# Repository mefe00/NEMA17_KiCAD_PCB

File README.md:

# NEMA17_KiCAD_PCB

Kartın üzerinde kullanılan bazı komponentlerin yanlış seçilmesinden dolayı kartın montajı gerçekleştirilemiyor. Aslında sadece TMC2208'in shild olarak seçilmesinden kaynaklı pin delikleri yanlış seçilmiştir. Kartın ikinci versiyonunda shild ve direkt TMC2208 çipi kullanılarak kart yenilenecektir.

V2 buradan paylaşılacaktır.

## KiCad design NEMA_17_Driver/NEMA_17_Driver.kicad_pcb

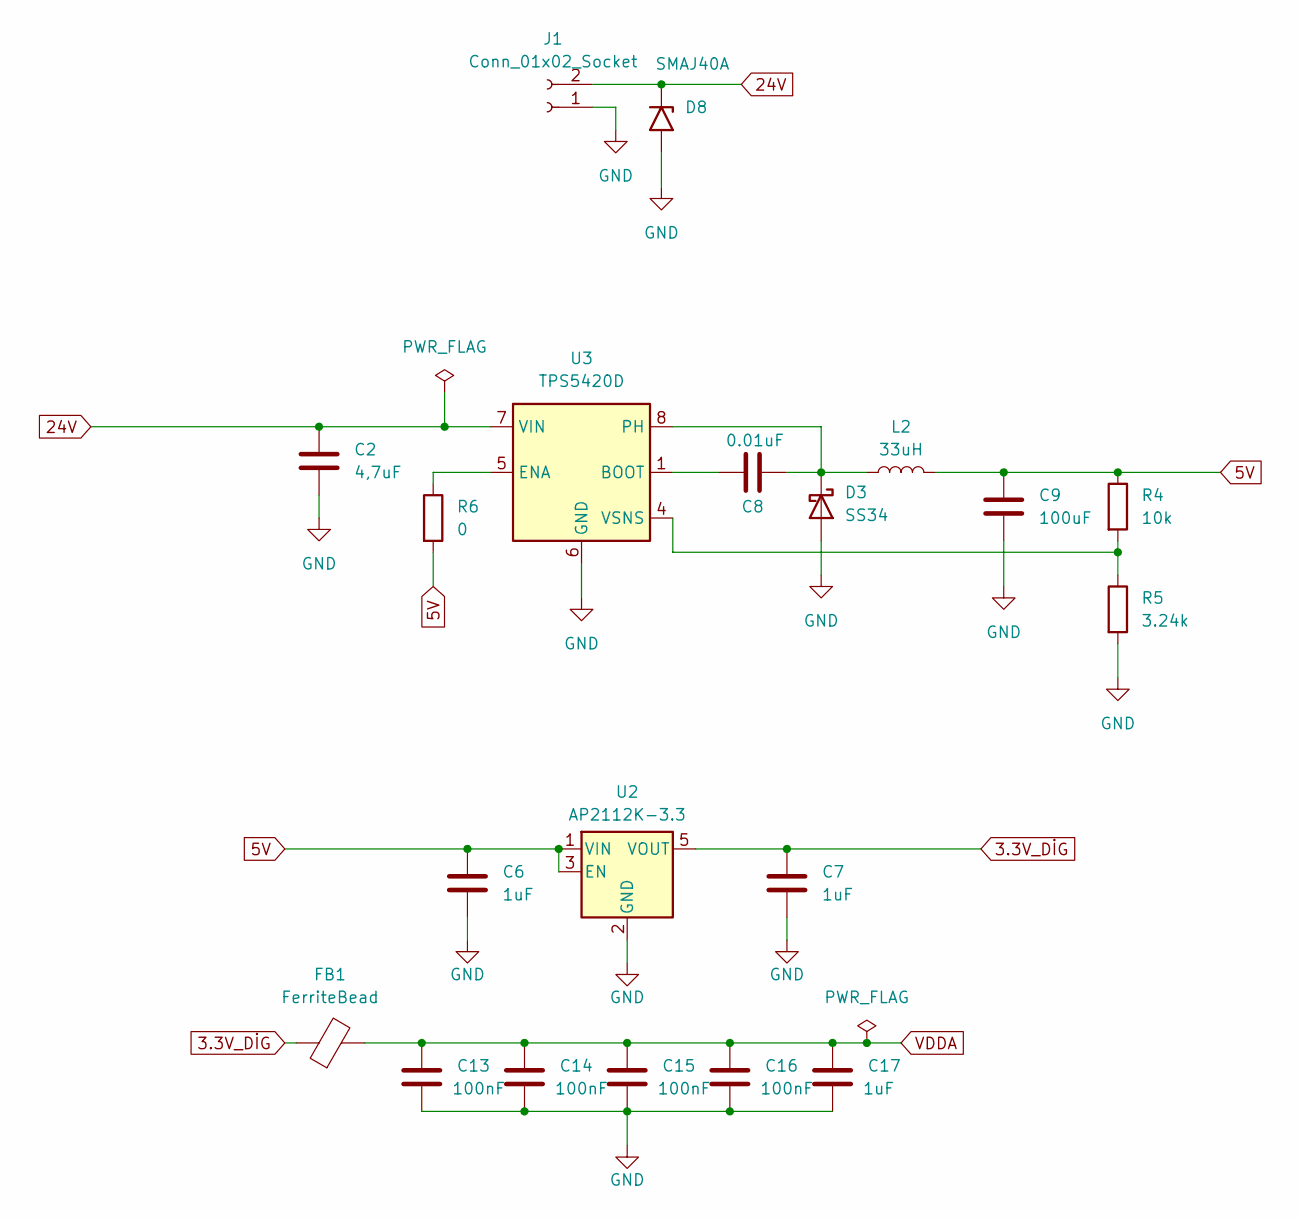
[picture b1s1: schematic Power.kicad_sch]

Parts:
C2: 4,7uF; C_Elec_8x10.2
C6, C7, C17: 1uF; C_0402_1005Metric
C8: 0.01uF; C_0603_1608Metric
C9: 100uF; C_0805_2012Metric
C13, C14, C15, C16: 100nF; C_0402_1005Metric
D3: SS34; D_SMA
D8: SMAJ40A; D_SMA
FB1: FerriteBead; L_0402_1005Metric
J1: Conn_01x02_Socket; SolderWire-0.75sqmm_1x02_P7mm_D1.25mm_OD3.5mm
L2: 33uH; L_Murata_DEM3512C
R4: 10k; R_0402_1005Metric
R5: 3.24k; R_0402_1005Metric
R6: 0; D_0201_0603Metric
U2: AP2112K-3.3; SOT-23-5
U3: TPS5420D; SOIC-8_3.9x4.9mm_P1.27mm

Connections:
3.3V_DİG: C7.1, FB1.1, U2.5 (VOUT); also elsewhere on the board
5V: C6.1, C9.1, L2.2, R4.1, R6.2, U2.1 (VIN), U2.3 (EN); also elsewhere on the board
24V: C2.1, D8.1 (A1), J1.2, U3.7 (VIN); also elsewhere on the board
GND: C2.2, C6.2, C7.2, C9.2, C13.2, C14.2, C15.2, C16.2, C17.2, D3.2 (A), D8.2 (A2), J1.1, R5.2, U2.2 (GND), U3.6 (GND); also elsewhere on the board
unnamed: C8.2, D3.1 (K), L2.1, U3.8 (PH)
unnamed: C8.1, U3.1 (BOOT)
unnamed: R6.1, U3.5 (ENA)
unnamed: R4.2, R5.1, U3.4 (VSNS)
VDDA: C13.1, C14.1, C15.1, C16.1, C17.1, FB1.2; also elsewhere on the board

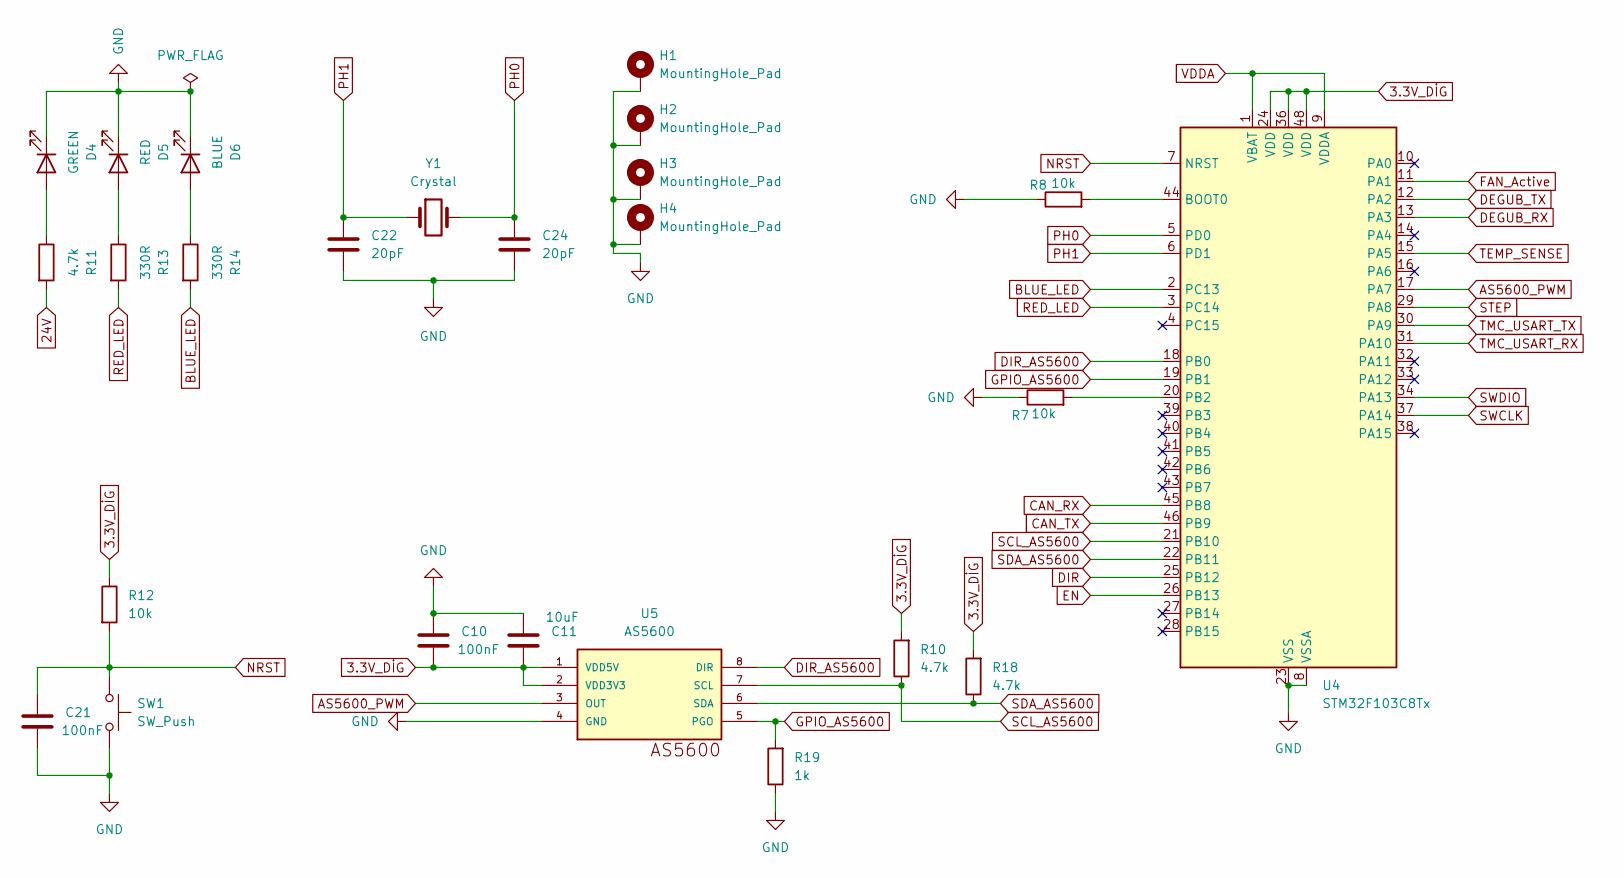
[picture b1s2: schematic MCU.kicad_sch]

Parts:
C10, C21: 100nF; C_0402_1005Metric
C11: 10uF; C_0402_1005Metric
C22, C24: 20pF; C_0603_1608Metric
D4: GREEN; LED_0402_1005Metric
D5: RED; LED_0402_1005Metric
D6: BLUE; LED_0402_1005Metric
H1, H2, H3, H4: MountingHole_Pad; MountingHole_3.5mm_Pad_Via
R7, R8, R12: 10k; R_0402_1005Metric
R10, R18: 4.7k; R_0402_1005Metric
R11: 4.7k; R_0603_1608Metric
R13, R14: 330R; R_0402_1005Metric
R19: 1k; R_0402_1005Metric
SW1: SW_Push; SW_Push_1P1T_NO_CK_KMR2
U4: STM32F103C8Tx; LQFP-48_7x7mm_P0.5mm
U5: AS5600; SOIC8
Y1: Crystal; Crystal_SMD_5032-2Pin_5.0x3.2mm

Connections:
3.3V_DİG: C10.2, C11.2, R10.2, R12.1, R18.2, U4.24 (VDD), U4.36 (VDD), U4.48 (VDD), U5.1 (VDD5V), U5.2 (VDD3V3); also elsewhere on the board
24V: R11.2; also elsewhere on the board
AS5600_PWM: U4.17 (PA7), U5.3 (OUT)
BLUE_LED: R14.2, U4.2 (PC13)
CAN_RX: U4.45 (PB8); also elsewhere on the board
CAN_TX: U4.46 (PB9); also elsewhere on the board
DEGUB_RX: U4.13 (PA3); also elsewhere on the board
DEGUB_TX: U4.12 (PA2); also elsewhere on the board
DIR: U4.25 (PB12); also elsewhere on the board
DIR_AS5600: U4.18 (PB0), U5.8 (DIR)
EN: U4.26 (PB13); also elsewhere on the board
FAN_Active: U4.11 (PA1); also elsewhere on the board
GND: C10.1, C11.1, C21.2, C22.2, C24.2, D4.1 (K), D5.1 (K), D6.1 (K), H1.1, H2.1, H3.1, H4.1, R7.1, R8.1, R19.1, SW1.2, U4.8 (VSSA), U4.23 (VSS), U4.35 (VSS), U4.47 (VSS), U5.4 (GND); also elsewhere on the board
GPIO_AS5600: R19.2, U4.19 (PB1), U5.5 (PGO)
NRST: C21.1, R12.2, SW1.1, U4.7 (NRST)
unnamed: D4.2 (A), R11.1
unnamed: D5.2 (A), R13.1
unnamed: D6.2 (A), R14.1
unnamed: R8.2, U4.44 (BOOT0)
unnamed: R7.2, U4.20 (PB2)
PH0: C24.1, U4.5 (PD0), Y1.2
PH1: C22.1, U4.6 (PD1), Y1.1
RED_LED: R13.2, U4.3 (PC14)
SCL_AS5600: R10.1, U4.21 (PB10), U5.7 (SCL)
SDA_AS5600: R18.1, U4.22 (PB11), U5.6 (SDA)
STEP: U4.29 (PA8); also elsewhere on the board
SWCLK: U4.37 (PA14); also elsewhere on the board
SWDIO: U4.34 (PA13); also elsewhere on the board
TEMP_SENSE: U4.15 (PA5); also elsewhere on the board
TMC_USART_RX: U4.31 (PA10); also elsewhere on the board
TMC_USART_TX: U4.30 (PA9); also elsewhere on the board
VDDA: U4.1 (VBAT), U4.9 (VDDA); also elsewhere on the board

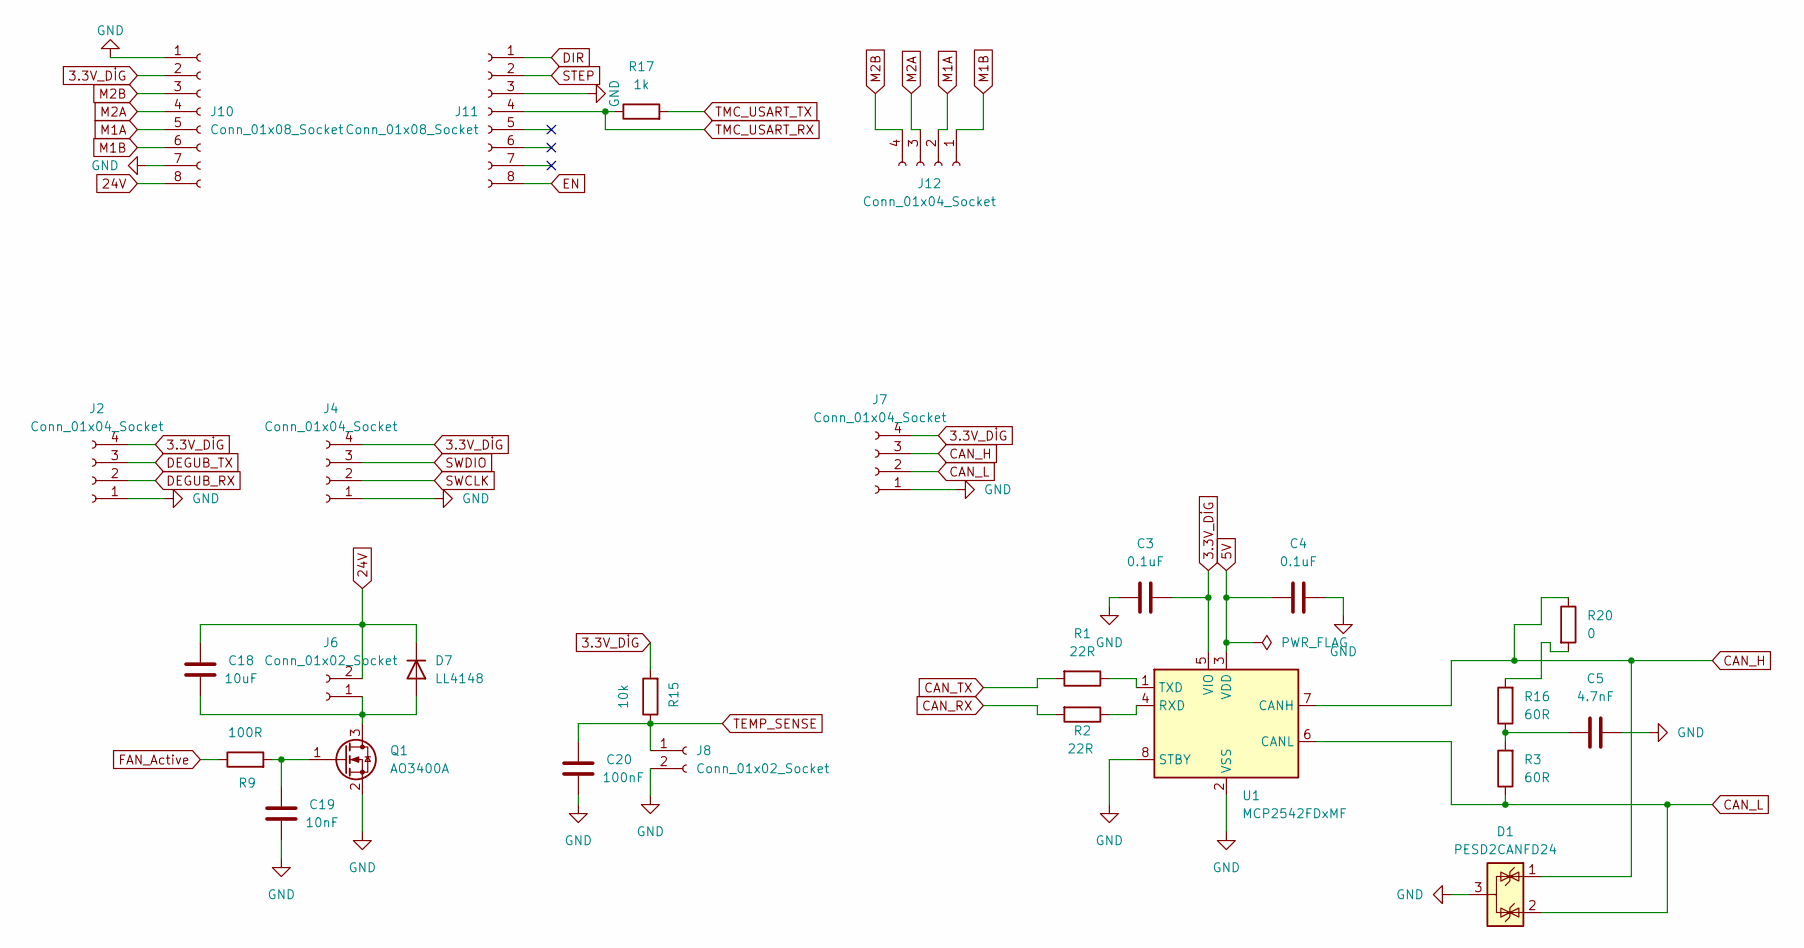
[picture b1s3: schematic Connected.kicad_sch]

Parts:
C3, C4: 0.1uF; C_0402_1005Metric
C5: 4.7nF; C_0402_1005Metric
C18: 10uF; C_0402_1005Metric
C19: 10nF; C_0402_1005Metric
C20: 100nF; C_0402_1005Metric
D1: PESD2CANFD24
D7: LL4148; D_MiniMELF
J2, J4: Conn_01x04_Socket; Hirose_DF13-04P-1.25DSA_1x04_P1.25mm_Vertical
J6, J8: Conn_01x02_Socket; Hirose_DF13-02P-1.25DSA_1x02_P1.25mm_Vertical
J7: Conn_01x04_Socket; Hirose_DF13-04P-1.25DS_1x04_P1.25mm_Horizontal
J10, J11: Conn_01x08_Socket; PinSocket_1x08_P2.00mm_Vertical
J12: Conn_01x04_Socket; Molex_KK-254_AE-6410-04A_1x04_P2.54mm_Vertical
Q1: AO3400A; SOT-23
R1, R2: 22R; R_0402_1005Metric
R3, R16: 60R; R_0402_1005Metric
R9: 100R; R_0402_1005Metric
R15: 10k; R_0402_1005Metric
R17: 1k; R_0402_1005Metric
R20: 0; R_0201_0603Metric
U1: MCP2542FDxMF; DFN-8-1EP_3x3mm_P0.65mm_EP1.55x2.4mm

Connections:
3.3V_DİG: C3.2, J2.4, J4.4, J7.4, J10.2, R15.2, U1.5 (VIO); also elsewhere on the board
5V: C4.1, U1.3 (VDD); also elsewhere on the board
24V: C18.1, D7.1 (K), J6.2, J10.8; also elsewhere on the board
CAN_H: D1.1 (K), J7.3, R20.1, U1.7 (CANH)
CAN_L: D1.2 (K), J7.2, R3.1, U1.6 (CANL)
CAN_RX: R2.2; also elsewhere on the board
CAN_TX: R1.2; also elsewhere on the board
DEGUB_RX: J2.2; also elsewhere on the board
DEGUB_TX: J2.3; also elsewhere on the board
DIR: J11.1; also elsewhere on the board
EN: J11.8; also elsewhere on the board
FAN_Active: R9.1; also elsewhere on the board
GND: C3.1, C4.2, C5.2, C19.2, C20.2, D1.3 (A), J2.1, J4.1, J7.1, J8.2, J10.1, J10.7, J11.3, Q1.2 (S), U1.2 (VSS), U1.8 (STBY), U1.9 (VSS); also elsewhere on the board
M1A: J10.5, J12.2
M1B: J10.6, J12.1
M2A: J10.4, J12.3
M2B: J10.3, J12.4
unnamed: C5.1, R3.2, R16.1
unnamed: C18.2, D7.2 (A), J6.1, Q1.3 (D)
unnamed: C19.1, Q1.1 (G), R9.2
unnamed: R16.2, R20.2
unnamed: R2.1, U1.4 (RXD)
unnamed: R1.1, U1.1 (TXD)
STEP: J11.2; also elsewhere on the board
SWCLK: J4.2; also elsewhere on the board
SWDIO: J4.3; also elsewhere on the board
TEMP_SENSE: C20.1, J8.1, R15.1; also elsewhere on the board
TMC_USART_RX: J11.4, R17.1; also elsewhere on the board
TMC_USART_TX: R17.2; also elsewhere on the board

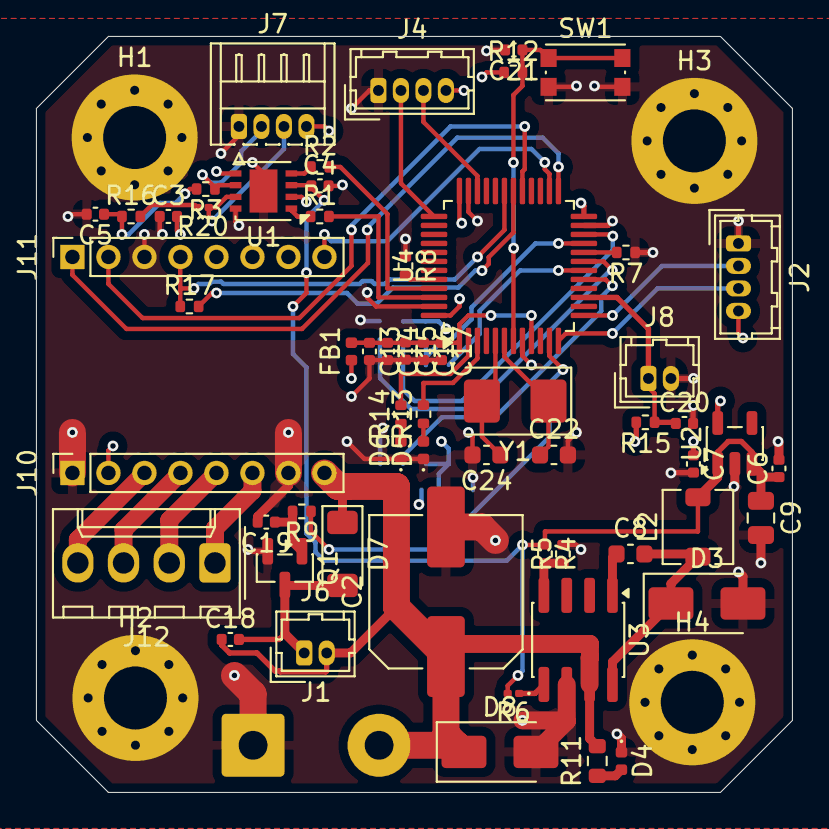
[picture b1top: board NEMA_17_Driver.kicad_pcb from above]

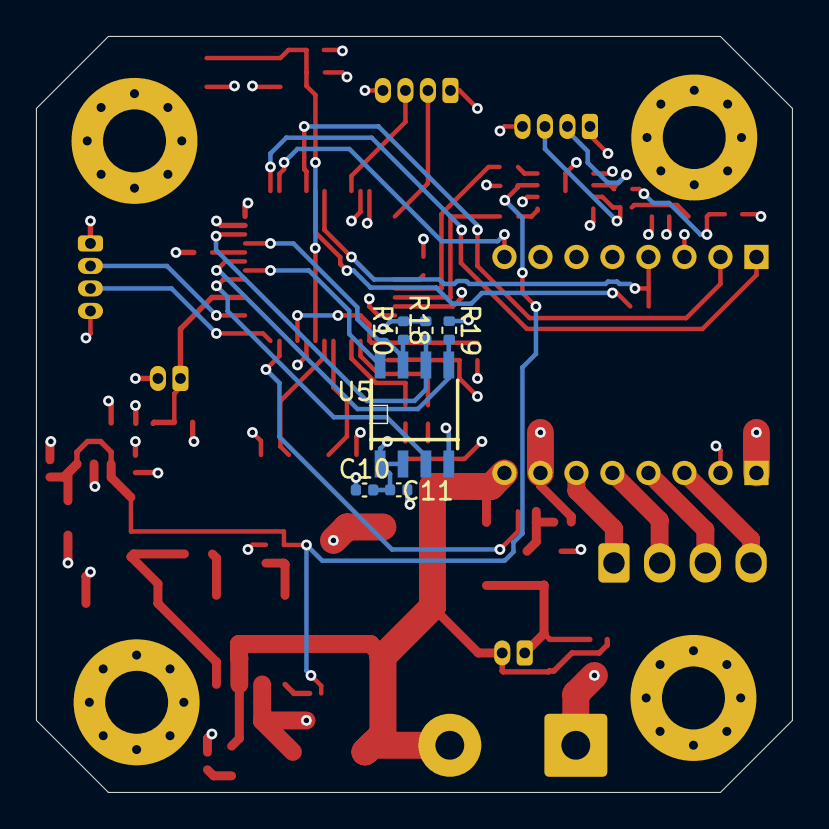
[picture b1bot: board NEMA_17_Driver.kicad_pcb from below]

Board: 4 copper layers, 42.0 x 42.0 mm, 70 parts (6 on the bottom side), 49 nets.

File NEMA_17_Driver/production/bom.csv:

Designator,Footprint,Quantity,Value,LCSC Part #
"C10, C13, C14, C15, C16, C20, C21",0402,7,100nF,
"C11, C18",0402,2,10uF,
"C17, C6, C7",0402,3,1uF,
C19,0402,1,10nF,
C2,C_Elec_8x10.2,1,"4,7uF",
"C22, C24",0603,2,20pF,
"C3, C4",0402,2,0.1uF,
C5,0402,1,4.7nF,
C8,0603,1,0.01uF,
C9,0805,1,100uF,
D3,D_SMA,1,SS34,
D4,0402,1,GREEN,
D5,0402,1,RED,
D6,0402,1,BLUE,
D7,D_MiniMELF,1,LL4148,
D8,D_SMA,1,SMAJ40A,
FB1,0402,1,FerriteBead,
J1,SolderWire-0.75sqmm_1x02_P7mm_D1.25mm_OD3.5mm,1,Conn_01x02_Socket,
"J10, J11",PinSocket_1x08_P2.00mm_Vertical,2,Conn_01x08_Socket,
J12,Molex_KK-254_AE-6410-04A_1x04_P2.54mm_Vertical,1,Conn_01x04_Socket,
"J2, J4",Hirose_DF13-04P-1.25DSA_1x04_P1.25mm_Vertical,2,Conn_01x04_Socket,
"J6, J8",Hirose_DF13-02P-1.25DSA_1x02_P1.25mm_Vertical,2,Conn_01x02_Socket,
J7,Hirose_DF13-04P-1.25DS_1x04_P1.25mm_Horizontal,1,Conn_01x04_Socket,
L2,L_Murata_DEM3512C,1,33uH,
Q1,SOT-23,1,AO3400A,
"R1, R2",0402,2,22R,
"R10, R18",0402,2,4.7k,
R11,0603,1,4.7k,
"R12, R15, R4, R7, R8",0402,5,10k,
"R13, R14",0402,2,330R,
"R16, R3",0402,2,60R,
"R17, R19",0402,2,1k,
"R20, R6",0201,2,0,
R5,0402,1,3.24k,
R9,0402,1,100R,
SW1,SW_Push_1P1T_NO_CK_KMR2,1,SW_Push,
U1,DFN-8-1EP_3x3mm_P0.65mm_EP1.55x2.4mm,1,MCP2542FDxMF,
U2,SOT-23-5,1,AP2112K-3.3,
U3,SOIC-8_3.9x4.9mm_P1.27mm,1,TPS5420D,
U4,LQFP-48_7x7mm_P0.5mm,1,STM32F103C8Tx,
U5,SOIC8,1,AS5600,
Y1,Crystal_SMD_5032-2Pin_5.0x3.2mm,1,Crystal,
